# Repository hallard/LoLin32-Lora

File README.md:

# ESP32 LoLin32 Lora Shield for RFM95 or RN2483

This shield is used to hold LoRa modules such as HopeRF [RFM95][4] or Mictrochip [RN2483][7] with WeMos ESP32 [LoLin32][20] boards it has the followong features:
- I2C Pullups placement
- Classic I2C connector with SCL/SDA and 3V3/GND reversable pin by solder pad
- Groove I2C connector
- Footprint for RFM95/96/98 or RN2483/RN2903 Lora module
- Footprint for choosing single Wire, SMA or u-FL Antenna type 
- 1 x WS2812B Type LED for visual indication
- 1 x Push Button
- Added footprint for Microchip 24AA02E64 64 bits serial number (DEVEUI)

**Take care that WeMos changed Lolin32 format**, you need to choose V1.0.0 that you can find on ebay, [banggood][10] or aliexpress. ~~Wemos does net seem to produce this board anymore~~. They're Back [here][11]. They do now Provide WeMos [Lolin32 Pro][21] or [Lolin32 Lite][22]

**So be sure to order board in the center of the picture above**

You can also check the shield for the [Lolin32 Lite][9] version. 

# Detailed Description

Look at the schematics for more informations.

SPI connexion is classic (MOSI/MISO/CLK), 

Other pins that may need be adapted into code (for example if you use TTN network gateway code) according to the following pinout

```
Lolin32      RFM9x Module
  IO5   <----> SEL 
  IO19  <----> MISO
  IO23  <----> MOSI
  IO18  <----> CLK
  IO27  <----> DIO0
  IO26  <----> DIO1
  IO4   <----> DIO2
  IO25  <----> RST
  IO35  <----> DIO5

Lolin32      RN2xx3 Module
  IO4   <----> RESET
  IO25  <----> RX
  IO35  <----> TX

Lolin32      Shield Feature
  IO22  <----> I2C SCL
  IO21  <----> I2C SDA
  IO13  <----> WS2812 LEDS
  IO15  <----> Push Button
```

**Do not forget to join (solder) the correct LoRa antenna trace** depending on module you place (RFM95 or RN2483), see picture below.

And as classic advice, **connect the LoRa antenna before powering** the board to avoid any damage to LoRa module

# Schematic  

# Firmware  

There is no firmware available, but you can have a large demo of features and a full working LoRa node (with RFM95) with this excellent [ESP32-Paxcounter](https://github.com/cyberman54/ESP32-Paxcounter/) software, it's a must see.

# Boards  

&nbsp;

You can order the PCB of this board at [PCBs.io][3]. PCBs.io give me some reward when you order my designed boards from their site. This is pretty good, because I can use these rewards to create and design new boards and order them for free, so if you don't care about PCB manufacturer please use PCBs.io.

# Assembled boards (V1.0)

## With RFM95

## With RN2483

# License

This work is licensed under a [Creative Commons Attribution-NonCommercial 4.0 International License](http://creativecommons.org/licenses/by-nc/4.0/)    
If you want to do commercial stuff with this project, please contact [CH2i company](https://ch2i.eu/en#support) so we can organize an simple agreement.

# Misc

See news and other projects on my [blog][2] 
 
[2]: https://hallard.me
[3]: https://PCBs.io/share/zO3Ye
[4]: http://www.hoperf.com/rf_transceiver/lora/
[5]: https://github.com/hallard/ESP-1ch-Gateway/
[6]: https://github.com/matthijskooijman/arduino-lmic/pull/34
[7]: https://www.microchip.com/wwwproducts/en/RN2483
[9]: https://github.com/hallard/LoLin32-Lite-Lora

[10]: http://www.banggood.com/WeMos-LOLIN32-V1_0_0-WiFi-Bluetooth-Board-Based-ESP-32-4MB-FLASH-p-1164252.html
[11]: https://www.aliexpress.com/store/product/WEMOS-LOLIN32-V1-0-0-wifi-bluetooth-board-based-ESP-32-4MB-FLASH/1331105_32808551116.html

[20]: https://wiki.wemos.cc/products:lolin32:lolin32
[21]: https://wiki.wemos.cc/products:lolin32:lolin32_pro
[22]: https://wiki.wemos.cc/products:lolin32:lolin32_lite

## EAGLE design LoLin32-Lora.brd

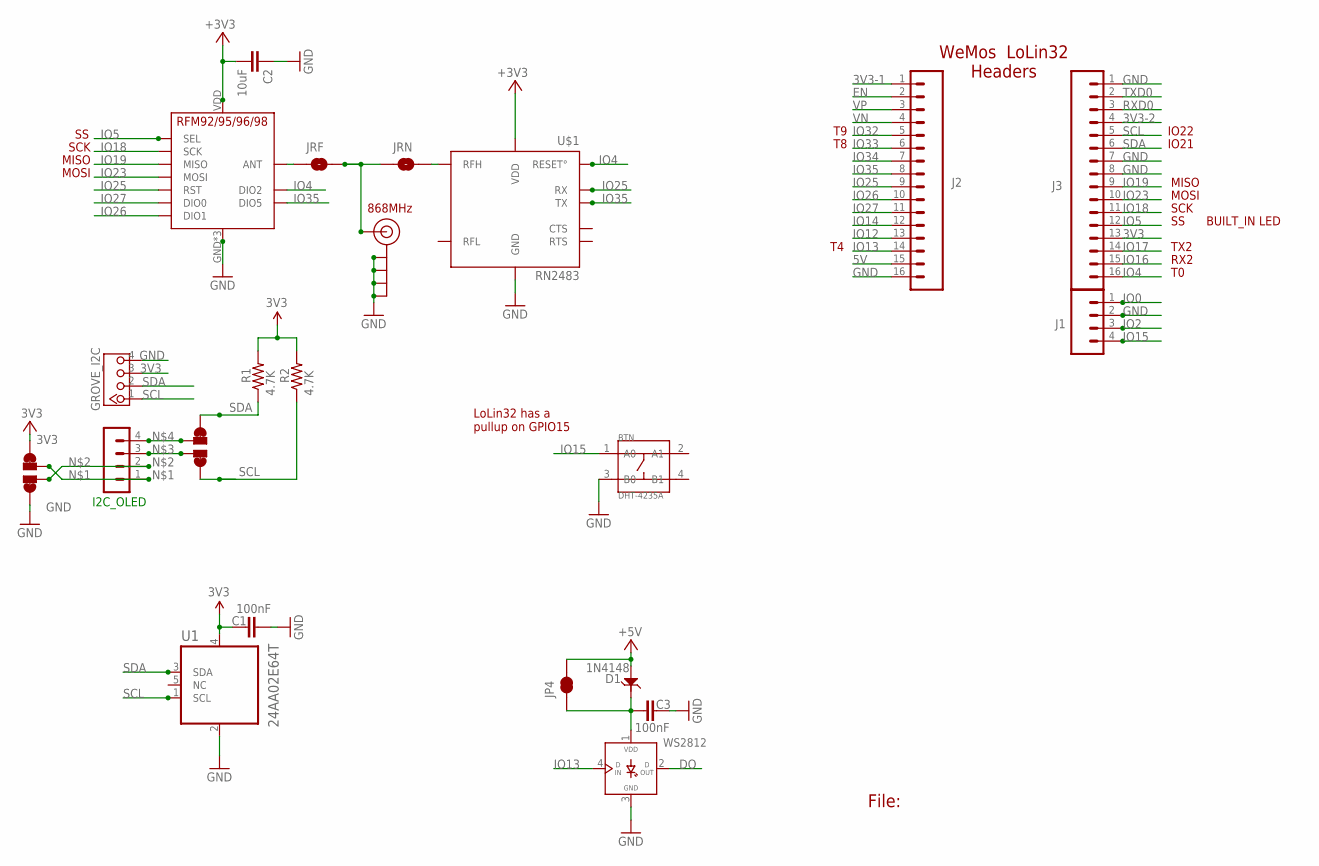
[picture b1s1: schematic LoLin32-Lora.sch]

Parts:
BTN: DHT-4235A; SW4-SMD-4.2X3.2X2.5MM
C1, C3: 100nF; 0805-CAP
C2: 10uF; 0805-CAP-LARGEPADS
D1: 1N4148; SOD123-2.7X1.6
GROVE_I2C: 4P-2.0; HW4-2.0
I2C_OLED: CON_HEADER_1X04'NO_LOCK'; 1X04_NO_LOCK
J1: M041X04_NO_SILK; 1X04_NO_SILK
J2, J3: M161X16_NO_SILK; 1X16_NO_SILK
J$2: ANTENNATINY; SMA_UFL_PAD_TINY
JP4: JUMPER-PAD-2-NC_BY_TRACE; PAD-JUMPER-2-NC_BY_TRACE_YES_SILK
JRF: JUMPER-PAD-2-NO; PAD-JUMPER-2-NO_NO_SILK
JRN: JUMPER-PAD-2-NO; PAD-JUMPER-2-NO_NO_SILK
R1, R2: 4.7K; 0805-RES
U1: 24AA02E64T; SOT95P270X145-5N
U$1: RN2483; RN2483_NOGPIO_868
U$2, U$3: PAD-JUMPER-SWAPSWAP; PAD-JUMPER-SWAP
U$5: RFM95
WS2812: WS2812B

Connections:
3V3: C2.2, GROVE_I2C.3, J3.13, R1.2, R2.2, U$1.VDD, U$1.VDD2 (VDD), U$2.4, U$2.44 (4), U$5.VDD (VCC)
3V3-1: J2.1
3V3-2: C1.1, J3.4, U1.4 (VCC)
5V: D1.1, J2.15, JP4.2
DO: WS2812.2 (DOUT)
EN: J2.2
GND: BTN.3 (B0), C1.2, C2.1, C3.2, GROVE_I2C.4, J1.2, J2.16, J3.1, J3.7, J3.8, J$2.GND1 (GND), J$2.GND2 (GND), J$2.GND3 (GND), J$2.GND4 (GND), U1.2 (VSS), U$1.GND, U$1.GND3 (GND), U$1.GND4 (GND), U$1.GND7 (GND), U$1.GND9 (GND), U$1.GND11 (GND), U$1.GND12 (GND), U$2.1, U$2.11 (1), U$5.GND, U$5.GND1 (GND), U$5.GND2 (GND), WS2812.3 (GND)
IO0: J1.1
IO2: J1.3
IO4: J3.16, U$1.RESET°, U$5.DIO2
IO5: J3.12, U$5.NSS (SEL)
IO12: J2.13
IO13: J2.14, WS2812.4 (DIN)
IO14: J2.12
IO15: BTN.1 (A0), J1.4
IO16: J3.15
IO17: J3.14
IO18: J3.11, U$5.SCK
IO19: J3.9, U$5.MISO
IO23: J3.10, U$5.MOSI
IO25: J2.9, U$1.UART_RX (RX), U$5.RST
IO26: J2.10, U$5.DIO1
IO27: J2.11, U$5.DIO0
IO32: J2.5
IO33: J2.6
IO34: J2.7
IO35: J2.8, U$1.UART_TX (TX), U$5.DIO5
unnamed: I2C_OLED.1, U$2.3
unnamed: I2C_OLED.2, U$2.2
unnamed: I2C_OLED.3, U$3.2
unnamed: I2C_OLED.4, U$3.3
unnamed: JRN.2, U$1.RFH
unnamed: JRF.1, U$5.ANT
unnamed: J$2.ANT1 (SIGNAL), J$2.ANT2 (SIGNAL), J$2.ANT3 (SIGNAL), JRF.2, JRN.1
RXD0: J3.3
SCL: GROVE_I2C.1, J3.5, R2.1, U1.1 (SCL), U$3.1, U$3.11 (1)
SDA: GROVE_I2C.2, J3.6, R1.1, U1.3 (SDA), U$3.4, U$3.44 (4)
TXD0: J3.2
VLED: C3.1, D1.2, JP4.1, WS2812.1 (VDD)
VN: J2.4
VP: J2.3

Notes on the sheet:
File:
WeMos LoLin32 Headers
868MHz
MOSI
MISO
SCK
LoLin32 has a pullup on GPIO15
IO21
IO22
RX2
TX2
BUILT_IN LED

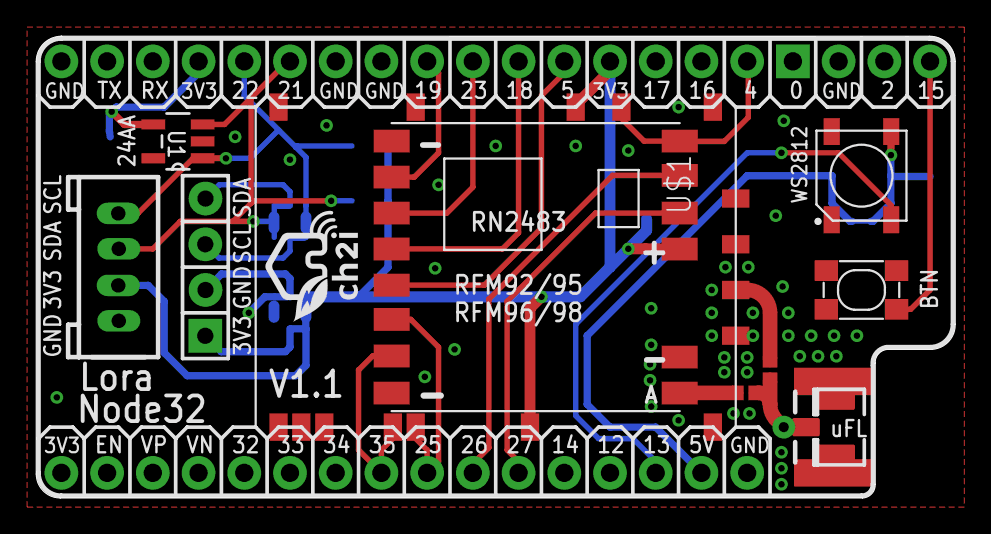
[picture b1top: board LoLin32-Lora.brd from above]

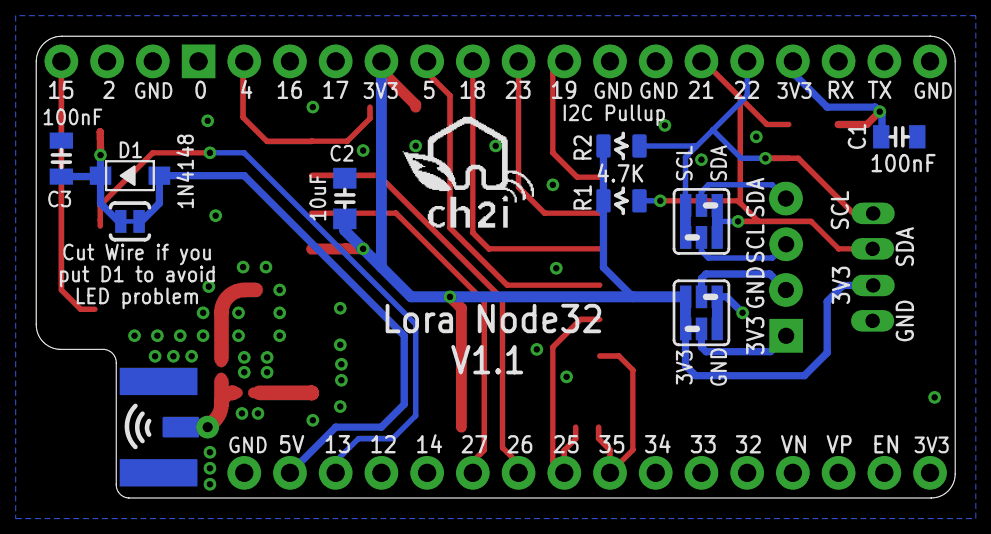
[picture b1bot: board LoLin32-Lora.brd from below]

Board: 2 copper layers, 51.1 x 25.7 mm, 24 parts (10 on the bottom side), 25 nets.

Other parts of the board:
U$4: LOGO_CH2I_75MM
U$6: LOGO_C2I_015

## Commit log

2017-08-04 :circus_tent: Added .gitattributes
2017-08-04 Creation
2017-08-04 Image Link
2018-03-25 Bump to V1.1
2018-03-26 Added Pictures
2018-03-26 Cosmetic
2018-03-26 Added board warning
2018-03-26 Added doc on LoRa antenna solder pad
2018-03-26 Syntax
2018-03-27 Added link to PAXCounter
2018-03-28 Added official link

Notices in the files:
parts and their libraries:
SparkFun-Connectors: Licensing: Creative Commons ShareAlike 4.0 International - https://creativecommons.org/licenses/by-sa/4.0
